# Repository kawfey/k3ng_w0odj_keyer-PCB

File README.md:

# k3ng_w0odj_keyer-PCB

Original K3NG CW Keyer PCB created with Kicad by W0ODJ. https://groups.io/g/radioartisan/message/8825

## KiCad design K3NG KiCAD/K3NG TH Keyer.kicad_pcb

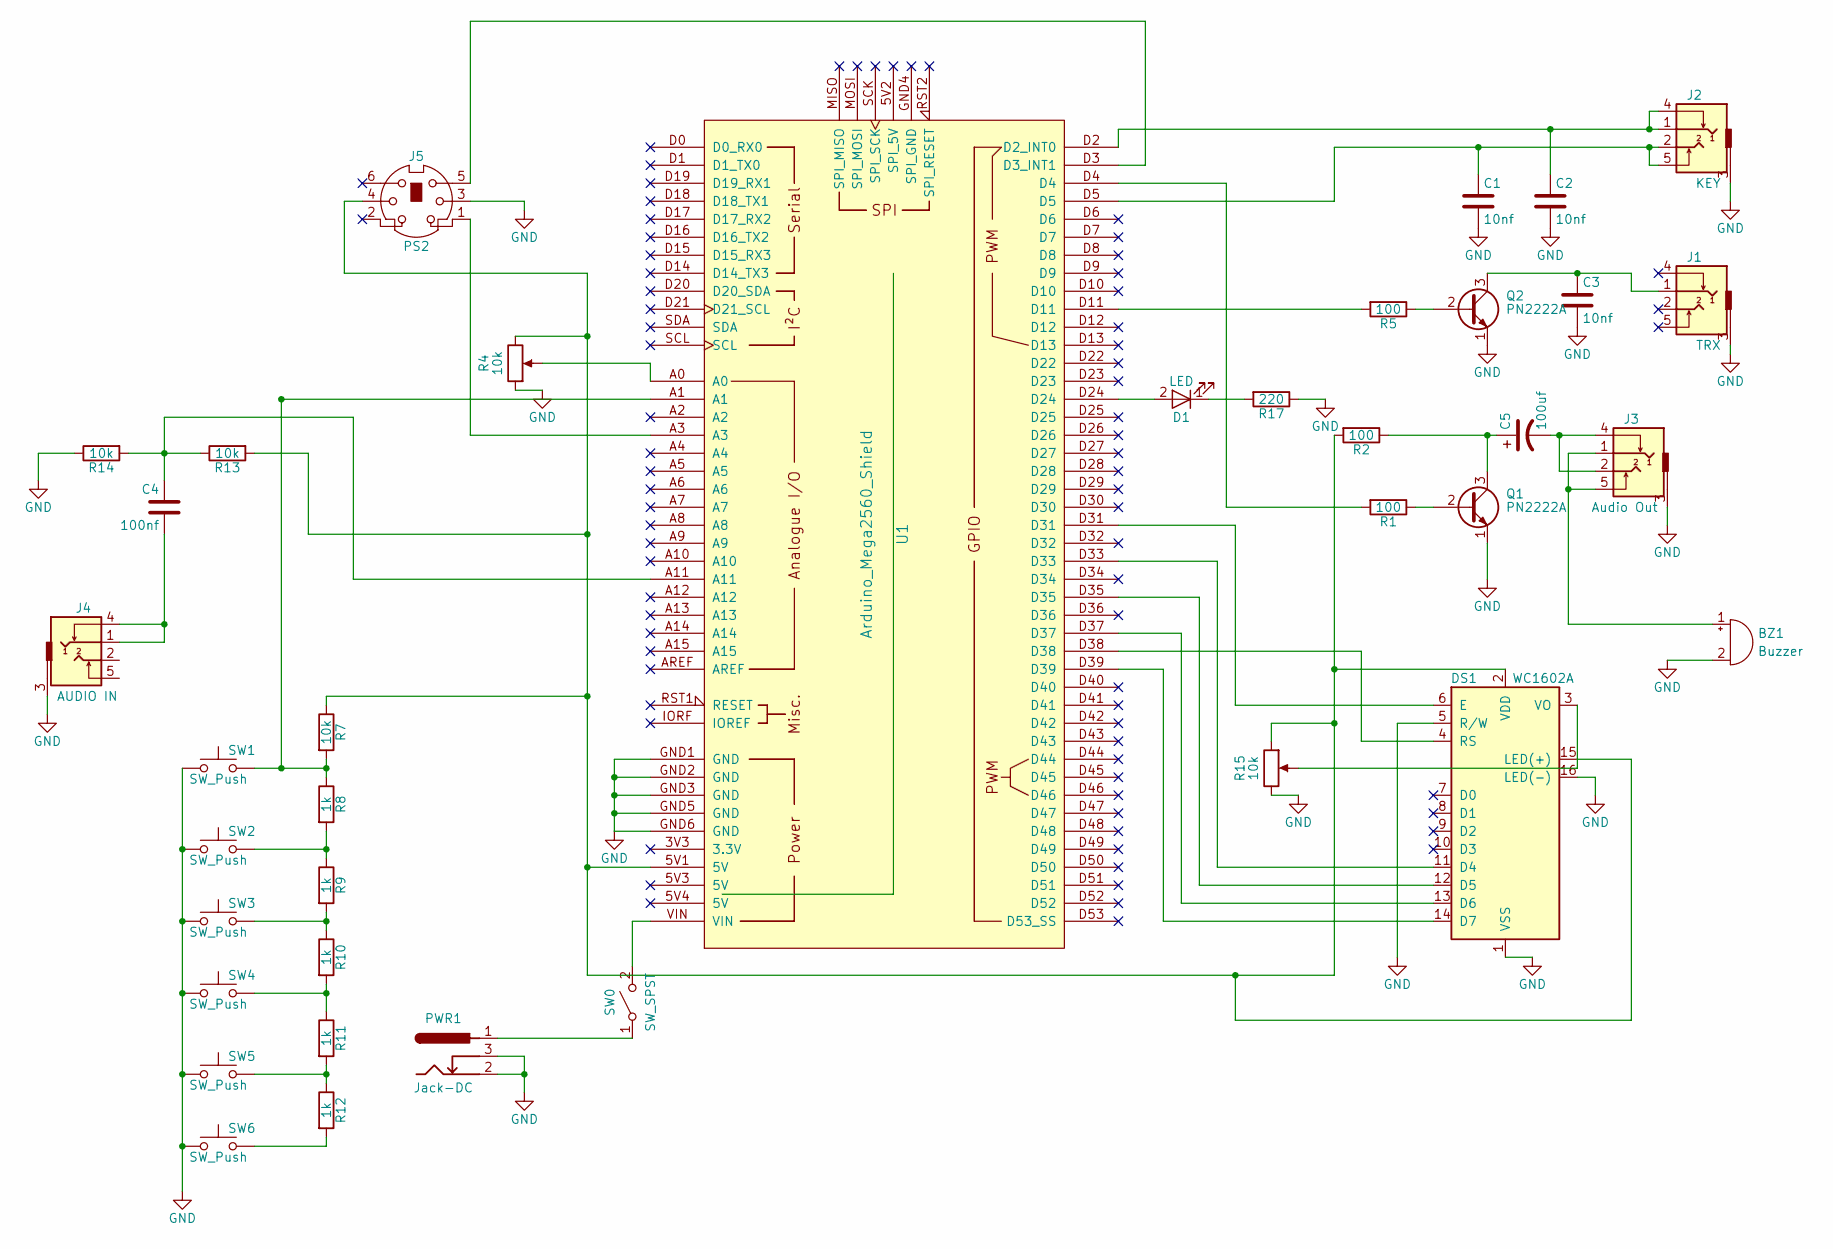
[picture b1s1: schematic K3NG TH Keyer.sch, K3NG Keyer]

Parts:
BZ1: Buzzer; Buzzer_15x7.5RM7.6; Mouser# 810-SD1614T5-B1
C1, C2, C3: 10nf; C_Disc_D5.0mm_W2.5mm_P5.00mm; Mouser# 810-FA24NP2E103JNU06
C4: 100nf; C_Disc_D5.0mm_W2.5mm_P5.00mm; Mouser# 80-C330C104J2H9170TR
C5: 100uf; CP_Radial_D8.0mm_P3.50mm; Mouser# 598-107RSS025M
D1: LED; LED_D3.0mm
DS1: WC1602A; Mouser# 763-0216K1Z-FSW-FBW
J1: TRX; Tayda_3.5mm_stereo_TRS_jack_A-853; Mouser# 490-SJ1-3525NG
J2: KEY; Tayda_3.5mm_stereo_TRS_jack_A-853; Mouser# 490-SJ1-3525NG
J3: Audio Out; Tayda_3.5mm_stereo_TRS_jack_A-853; Mouser# 490-SJ1-3525NG
J4: AUDIO IN; Tayda_3.5mm_stereo_TRS_jack_A-853; Mouser# 490-SJ1-3525NG
J5: PS2; din6-schurter-4850261; Mouser# 490-MD-60SM
PWR1: Jack-DC; BARREL_JACK; Mouser# 992-CON-SOCJ-2155
Q1, Q2: PN2222A; TO-92_Molded_Narrow; Mouser# 610-PN2222A
R1, R2, R5: 100; R_Axial_DIN0207_L6.3mm_D2.5mm_P10.16mm_Horizontal; Mouser# 279-CFR100J100R
R4: 10k; Potentiometer_Bourns_PTV09A-2_Vertical; Mouser# 858-P090L-03F20BR10K
R7, R13, R14: 10k; R_Axial_DIN0207_L6.3mm_D2.5mm_P10.16mm_Horizontal; Mouser# 660-CF1/4CT52R103J
R8, R9, R10, R11, R12: 1k; R_Axial_DIN0207_L6.3mm_D2.5mm_P10.16mm_Horizontal; Mouser# 603-CFR-25JR-521K
R15: 10k; Potentiometer_Bourns_3296W_3-8Zoll_Inline_ScrewUp; Mouser# 652-3296W-1-103LF
R17: 220; R_Axial_DIN0207_L6.3mm_D2.5mm_P10.16mm_Horizontal
SW0: SW_SPST; SW_E-Switch_EG1224_SPDT_Angled; Mouser# 612-EG1224
SW1, SW2, SW3, SW4, SW5, SW6: SW_Push; SW_PUSH_6mm; Mouser# 688-SKHHBV
U1: Arduino_Mega2560_Shield; Mouser# 782-A000067

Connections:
GND: BZ1.2 (+), C1.2, C2.2, C3.2, DS1.1 (VSS), DS1.5 (R/W), DS1.16 (LED(-)), J1.3, J2.3, J3.3, J4.3, J5.3, PWR1.2, PWR1.3, Q1.1 (E), Q2.1 (E), R4.1, R14.1, R15.3, R17.1, SW1.1, SW2.1, SW3.1, SW4.1, SW5.1, SW6.1, U1.GND1 (GND), U1.GND2 (GND), U1.GND3 (GND), U1.GND5 (GND), U1.GND6 (GND)
unnamed: BZ1.1 (-), J3.1, J3.5
unnamed: C1.1, J2.2, J2.5, U1.D5
unnamed: C2.1, J2.1, J2.4, U1.D2 (D2_INT0)
unnamed: C3.1, J1.1, Q2.3 (C)
unnamed: C4.1, R13.1, R14.2, U1.A11
unnamed: C4.2, J4.1, J4.4
unnamed: C5.1, Q1.3 (C), R2.1
unnamed: C5.2, J3.2, J3.4
unnamed: D1.1 (K), R17.2
unnamed: D1.2 (A), U1.D24
unnamed: DS1.3 (VO), R15.2
unnamed: DS1.4 (RS), U1.D38
unnamed: DS1.6 (E), U1.D31
unnamed: DS1.11 (D4), U1.D33
unnamed: DS1.12 (D5), U1.D35
unnamed: DS1.13 (D6), U1.D37
unnamed: DS1.14 (D7), U1.D39
unnamed: DS1.2 (VDD), DS1.15 (LED(+)), J5.4, R2.2, R4.3, R7.1, R13.2, R15.1, U1.5V1 (5V)
unnamed: J5.1, U1.A3
unnamed: J5.5, U1.D3 (D3_INT1)
unnamed: PWR1.1, SW0.1 (A)
unnamed: Q1.2 (B), R1.1
unnamed: Q2.2 (B), R5.1
unnamed: R1.2, U1.D4
unnamed: R4.2, U1.A0
unnamed: R5.2, U1.D11
unnamed: R7.2, R8.1, SW1.2, U1.A1
unnamed: R8.2, R9.1, SW2.2
unnamed: R9.2, R10.1, SW3.2
unnamed: R10.2, R11.1, SW4.2
unnamed: R11.2, R12.1, SW5.2
unnamed: R12.2, SW6.2
unnamed: SW0.2 (B), U1.VIN

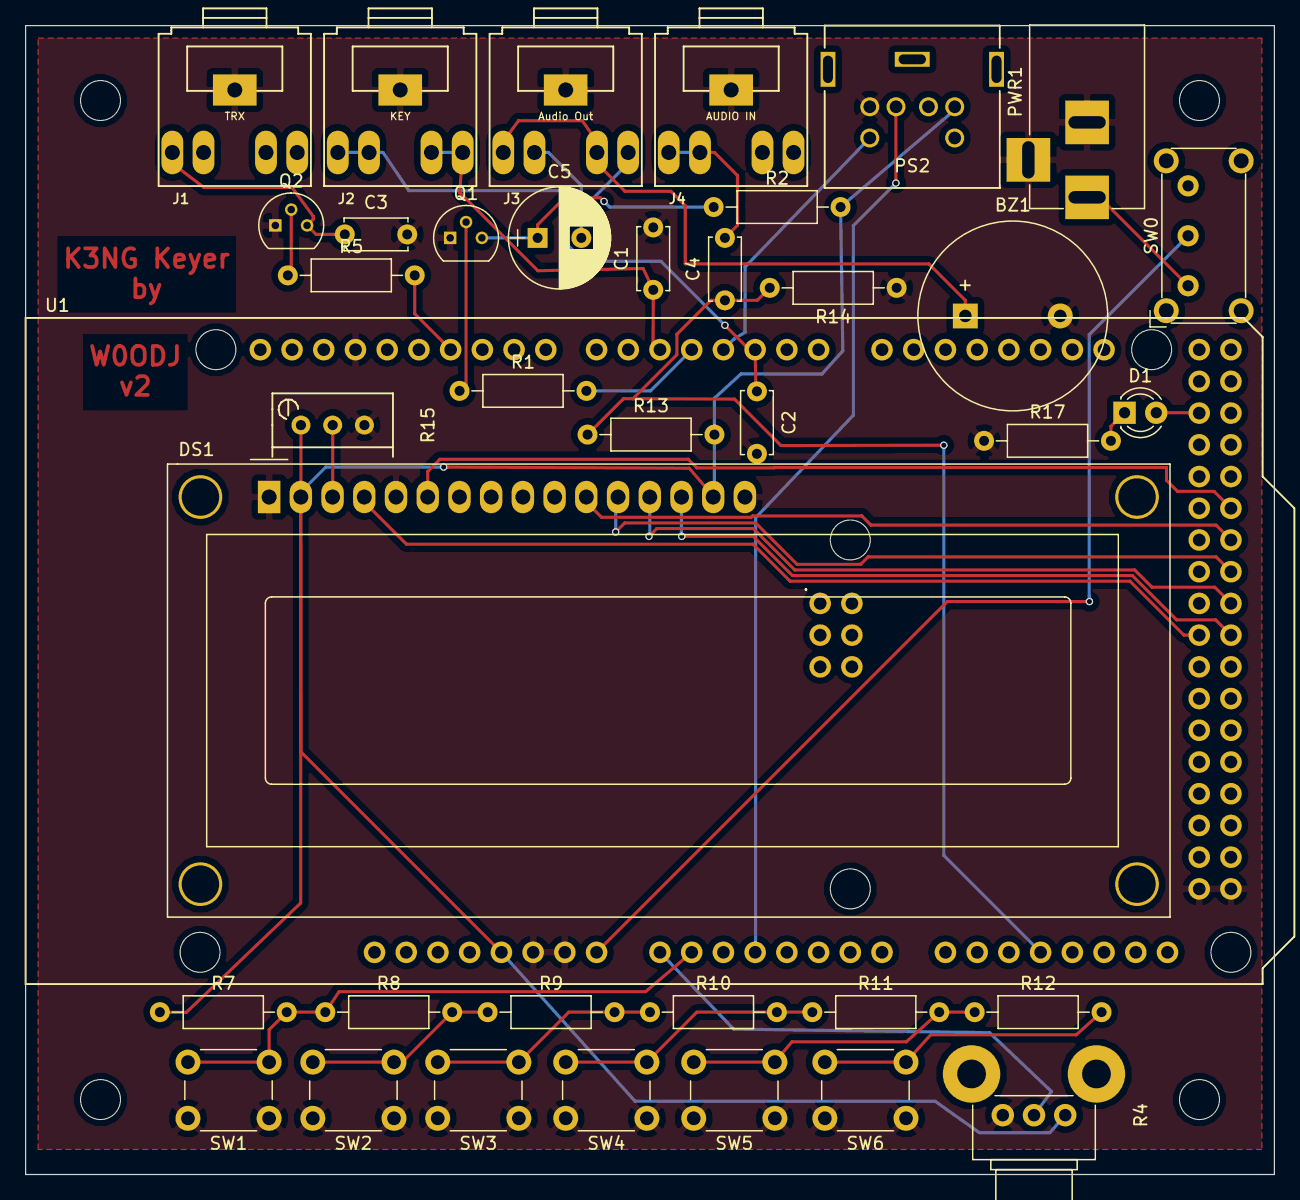
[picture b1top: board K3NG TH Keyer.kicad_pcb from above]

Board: 2 copper layers, 100.0 x 92.0 mm, 38 parts (0 on the bottom side), 34 nets.

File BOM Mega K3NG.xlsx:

Qty | Value | Ref | Description | Price Ea | Price Total | Mouser # / Link
1.0 |  | BZ1 | Buzzer | 2.18 | 2.18 | 810-SD1614T5-B1
3.0 | 10nf | C1, C2, C3 | Ceramic Capacitor | 0.03 | 0.09 | https://www.taydaelectronics.com/capacitors/monolithic-ceram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
1.0 | 100nf | C4 | Ceramic Capacitor | 0.06 | 0.06 | https://www.taydaelectronics.com/capacitors/monolithic-ceram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
1.0 | 100uf | C5 | Electrolytic Capacitor | 0.03 | 0.03 | https://www.taydaelectronics.com/capacitors/electrolytic-cap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
4.0 |  | J1, J2, J3, J4 | TRS Stereo Jack **NOTE FOOTPRINT** | 0.12 | 0.48 | https://www.taydaelectronics.com/hardware/3-5mm-plugs-jacks/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
1.0 |  | J5 | MINI-DIN 6 – PS/2 socket | 1.42 | 1.42 | 490-MD-60SM
1.0 |  | PWR1 | 2.1mm DC Barrel Socket | 0.16 | 0.16 | https://www.taydaelectronics.com/hardware/dc-power/dc-power-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
2.0 | PN2222A | Q1, Q2 | TO-92 Transistor | 0.05 | 0.1 | https://www.taydaelectronics.com/pn2222a-pn2222-transistor-n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
3.0 | 100.0 | R1, R2, R5 | ¼W Resistor | 0.01 | 0.03 | https://www.taydaelectronics.com/resistors/1-4w-carbon-film-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
1.0 | 10k | R4 | Bourns 10k Linear Pot (PTV09A) | 0.82 | 0.82 | 858-P090L-03F20BR10K
3.0 | 10k | R7, R13, R14 | ¼W Resistor | 0.01 | 0.03 | https://www.taydaelectronics.com/resistors/1-4w-carbon-film-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
1.0 | 220.0 | R17 | ¼W Resistor | 0.01 | 0.01 | https://www.taydaelectronics.com/resistors/1-4w-carbon-film-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
5.0 | 1k | R8, R9, R10, R11, R12 | ¼W Resistor | 0.01 | 0.05 | https://www.taydaelectronics.com/resistors/1-4w-carbon-film-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
1.0 | 10k | R15 | Bourns 10k 3296W TrimPot | 0.28 | 0.28 | https://www.taydaelectronics.com/potentiometer-variable-resi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
1.0 | SPST | SW0 | SPST Right Angle Slide Switch | 0.72 | 0.72 | 612-EG1224
6.0 | Tact Switch | SW1, SW2, SW3, SW4, SW5, SW6 | 6mm Tacticle Switch | 0.05 | 0.3 | https://www.taydaelectronics.com/tact-switch-6-6mm-8mm-throu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
1.0 | Arduino | U1 | Arduino Mega 2560 | 12.98 | 12.98 | https://www.ebay.com/itm/MEGA-2560-R3-Board-ATmega2560-16AU-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
5.0 |  | U1*, DSP1* | Single Straight Pin Header 2.54 | 0.15 | 0.75 | https://www.taydaelectronics.com/connectors-sockets/pin-head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
1.0 |  | U1* | Double Straight Pin Header 2.54 | 0.32 | 0.32 | https://www.taydaelectronics.com/connectors-sockets/pin-head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
1.0 | LED | D1 | 3mm LED | 0.04 | 0.04 | https://www.taydaelectronics.com/leds/round-leds/3mm-leds/bl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
1.0 | LCD | DS1 | 1602 LCD Display | 2.09 | 2.09 | https://www.ebay.com/itm/New-Blue-IIC-I2C-TWI-1602-16x2-LCD-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
4.0 |  | DS1* | Standoff (spacer) | 0.06 | 0.24 | https://www.ebay.com/itm/25-100pcs-Black-Plastic-Nylon-M2-M3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
12.0 |  | U1*, DS1* | Standoff (screw) | 0.03 | 0.36 | https://www.ebay.com/itm/25-100pcs-Black-Plastic-Nylon-M2-M3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
1.0 |  | Knob | Knob for R4 | 0.49 | 0.49 | https://www.taydaelectronics.com/hardware/knobs-8688/kn1360-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
1.0 | PCB | PCB | K3NG PCB | 2.2 | 2.2 | JLCPCB
 |  |  | Totals |  | 26.23
10.0 | Keyers |  | Combined Total |  | 262.3
 |  |  | Total - (minus Arduino & Screen) | 11.16 | 111.6

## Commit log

2018-12-13 Imported files from message
    Source: https://groups.io/g/radioartisan/message/8825
2018-12-13 add kicad to readme
